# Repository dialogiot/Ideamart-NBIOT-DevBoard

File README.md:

### About the Board

The board is developed based on the [SIM7000C](http://www.simcomm2m.com/En/module/detail.aspx?id=167) and [SIM7000E](http://www.simcomm2m.com/En/module/detail.aspx?id=168) Modules as well as the Microcontroller ATMega 328 based on the most popular Arduino UNO PIN layout. Therefore this board is compatible with any shield that is compatible with the Arduino UNO

### Distribution
Any one can destribute or modify this deign. but originated souce should be published

### NB-IOT /GPS sample and SDK
[https://github.com/dialogiot/Dialog_NB-IOT_CAT-M](https://github.com/dialogiot/Dialog_NB-IOT_CAT-M)

#### Drivers

Download the [USB Drivers](https://github.com/botletics/SIM7000-LTE-Shield/wiki/SIM7000-USB-Drivers)
Note: Windows 10 users should use the Windows 8 Drivers

</img>

[View Image](https://idealab.ideamart.io/NBIOT-Dev-Board/img/features/board-diagram.jpg)

|No|PIN |Description|
|---|---|---|
| 1 | USB Port | Programing USB port for ATMEL Chip - PC driver may be required. Use Arduino USB cable or USB printer wire to connect with PC |
| 2 | FTDI | FTDI USB to Serial Converter FT232RL chip |
| 3 | LED2 | User programable LED |
| 4 | PIN Headers | Programable PIN headers to connect with micro controller. (Diagram 2 for more details) |
| 5 | Level Shifter | 1.8V to 5V voltage level shifter |
| 6 | SIM7000 | SIM7000 NB-IOT/eMTC/GSM/LTE Modem and GNSS Receiver |
| 7 | RF Antenna | RF mobile network antenna port for SIM7000 (u.fL) |
| 8 | GPS Antenna | GPS signal antenna port for SIM7000 (u.fL) |
| 9 | PPTC | PPTC resettable fuse for USB input over current protection (max 500mA) |
| 10 | DC Input | 2.1mm 7-12V DC power input |
| 11 | RESET | ATMEGA328P micro controller reset button |
| 12 | 3.3V Regulator | Lm1117 3.3V low dropout linear regulator (max 800ma)|
| 13 | 5V Regulator | LM1117 5V low dropout linear regulator (max 800mA) |
| 14 | PIN Headers | Programable PIN headers to connect with micro controller.(Diagram 2 for more details) |
| 15 | ATMEGA328P | ATMEGA328P micro controller |
| 16 | Power LED | Power indicator LED |
| 17 | ICSP Header | ICSP Header for Arduino programming |
| 18 | Modem Reset | SIM7000 modem hardware reset button |
| 19 | STAT LED | SIM7000 modem STAT LED indicator |
| 20 | Modem USB | SIM7000 modem USB port - firmware upgrade - Modem debug |
| 21 | PWR KEY | SIM7000 modem power key - Press 1.5sec to power up/down |
| 22 | Net Light | Power indicator LED |

## 2 What you Should know about the board

- ATMEGA328P µCU with FTDI USB to serial converter
- Same pinout as Arduino UNO
- Compatible with any Arduino UNO shield
- Programable with Arduino IDE
- NB-IoT/GSM/LTE/eMTC enabled SIM7000C/SIM7000E module onboard
- Separate USB interface for SIM7000 module
- GNSS (GPS,GLONASS and BeiDou/Compass, Galileo, QZSS)enabled 

> Separate USB interface can only be used for SIM7000 debug and firmware upgrades

- SIM7000C FDD-LTE B1/B3/B5/B8
- SIM7000E Tri-Band FDD-LTE B3/B8/B20/B28
- GSM/GPRS/EDGE 900/1800 MHz
- GNSS (GPS,GLONASS and BeiDou/Compass, Galileo, QZSS)
- LTE CAT-M1(eMTC) Uplink up to 375kbps, Downlink up to 300kbps
- NB-IoT Uplink up to 66kbps, Downlink up to 34kbps
- EDGE Class Uplink up to 236.8Kbps, Downlink up to 236.8Kbps
- GPRS Uplink up to 85.6Kbps, Downlink up to 85.6Kbps

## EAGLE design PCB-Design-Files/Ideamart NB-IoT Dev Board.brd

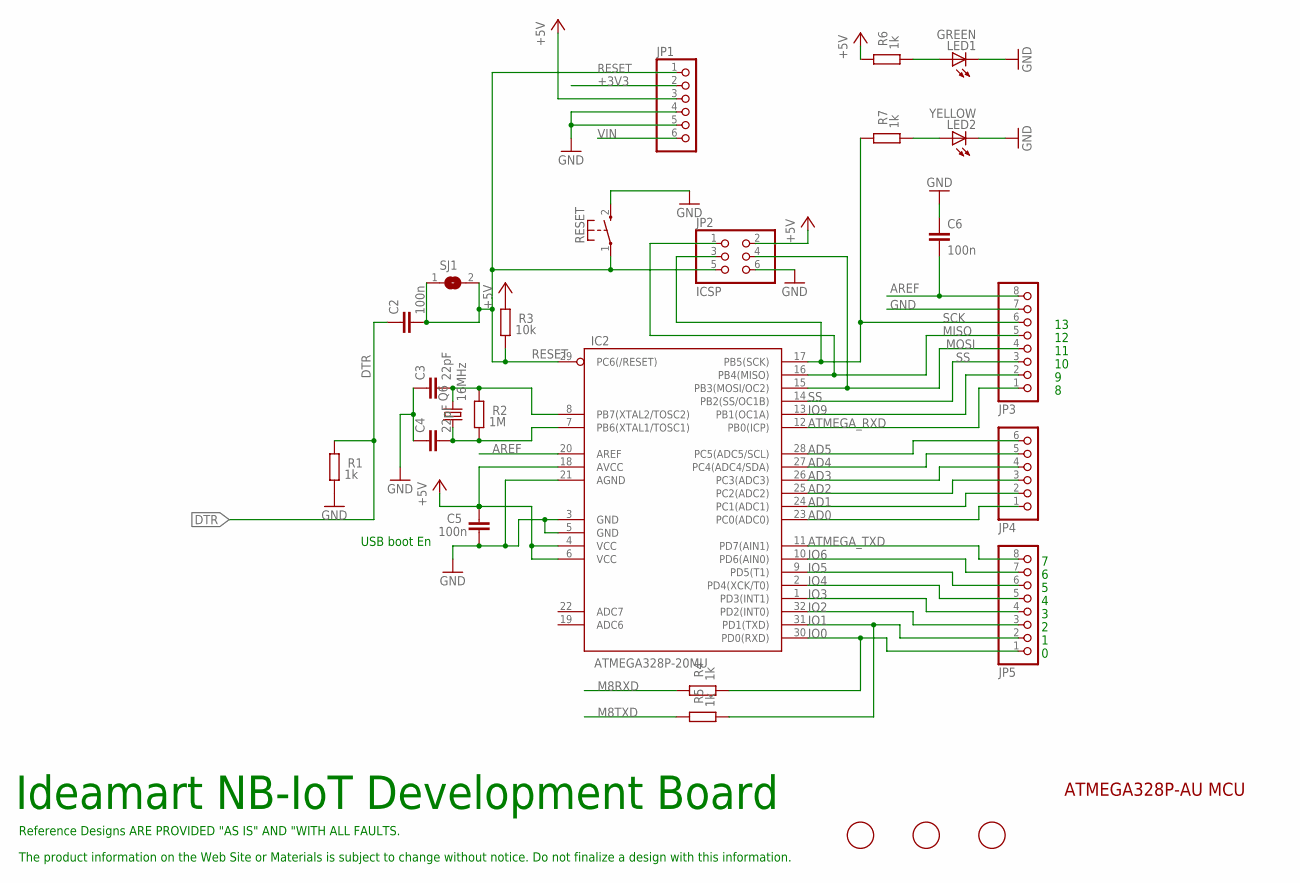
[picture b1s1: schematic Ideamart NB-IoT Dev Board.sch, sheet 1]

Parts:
C2, C5, C6: 100n; C0805
C3, C4: 22pF; C0805
IC2: ATMEGA328P-20MU; TQFP32-08
JP1, JP4: PINHD-1X6; 1X06
JP2: ICSP; 2X03
JP3, JP5: PINHD-1X8; 1X08
LED1: GREEN; CHIP-LED0805
LED2: YELLOW; CHIP-LED0805
M1, M2, M3: FIDUCIALMOUNT; FIDUCIA-MOUNT
Q6: 16MHz; CTS406
R1, R4, R5, R6, R7: 1k; R0805
R2: 1M; R0805
R3: 10k; R0805
RESET: KSS-2EG4430
SJ1: SJ

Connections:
+3V3: JP1.2; also elsewhere on the board
+5V: C5.2, IC2.4 (VCC), IC2.6 (VCC), IC2.18 (AVCC), JP1.3, JP2.2, R3.2, R6.2; also elsewhere on the board
AD0: IC2.23 (PC0(ADC0)), JP4.1
AD1: IC2.24 (PC1(ADC1)), JP4.2
AD2: IC2.25 (PC2(ADC2)), JP4.3
AD3: IC2.26 (PC3(ADC3)), JP4.4
AD4: IC2.27 (PC4(ADC4/SDA)), JP4.5
AD5: IC2.28 (PC5(ADC5/SCL)), JP4.6
AREF: C6.2, IC2.20 (AREF), JP3.8
ATMEGA_RXD: IC2.12 (PB0(ICP)), JP3.1; also elsewhere on the board
ATMEGA_TXD: IC2.11 (PD7(AIN1)), JP5.8; also elsewhere on the board
DTR: C2.1, R1.2; also elsewhere on the board
GND: C3.1, C4.1, C5.1, C6.1, IC2.3 (GND), IC2.5 (GND), IC2.21 (AGND), JP1.4, JP1.5, JP2.6, JP3.7, LED1.C, LED2.C, R1.1, RESET.2 (S); also elsewhere on the board
IO0: IC2.30 (PD0(RXD)), JP5.1, R4.1
IO1: IC2.31 (PD1(TXD)), JP5.2, R5.1
IO2: IC2.32 (PD2(INT0)), JP5.3
IO3: IC2.1 (PD3(INT1)), JP5.4
IO4: IC2.2 (PD4(XCK/T0)), JP5.5
IO5: IC2.9 (PD5(T1)), JP5.6
IO6: IC2.10 (PD6(AIN0)), JP5.7
IO9: IC2.13 (PB1(OC1A)), JP3.2
M8RXD: R4.2; also elsewhere on the board
M8TXD: R5.2; also elsewhere on the board
MISO: IC2.16 (PB4(MISO)), JP2.1, JP3.5
MOSI: IC2.15 (PB3(MOSI/OC2)), JP2.4, JP3.4; also elsewhere on the board
unnamed: LED2.A, R7.1
unnamed: LED1.A, R6.1
RESET: C2.2, IC2.29 (PC6(/RESET)), JP1.1, JP2.5, R3.1, RESET.1, SJ1.1, SJ1.2
SCK: IC2.17 (PB5(SCK)), JP2.3, JP3.6, R7.2; also elsewhere on the board
SS: IC2.14 (PB2(SS/OC1B)), JP3.3
VIN: JP1.6; also elsewhere on the board
XTAL1: C4.2, IC2.7 (PB6(XTAL1/TOSC1)), Q6.1, R2.1
XTAL2: C3.2, IC2.8 (PB7(XTAL2/TOSC2)), Q6.3 (2), R2.2

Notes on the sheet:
Ideamart NB-IoT Development Board
USB boot En
Reference Designs ARE PROVIDED "AS IS" AND "WITH ALL FAULTS.
The product information on the Web Site or Materials is subject to change without notice. Do not finalize a design with this information.
ATMEGA328P-AU MCU

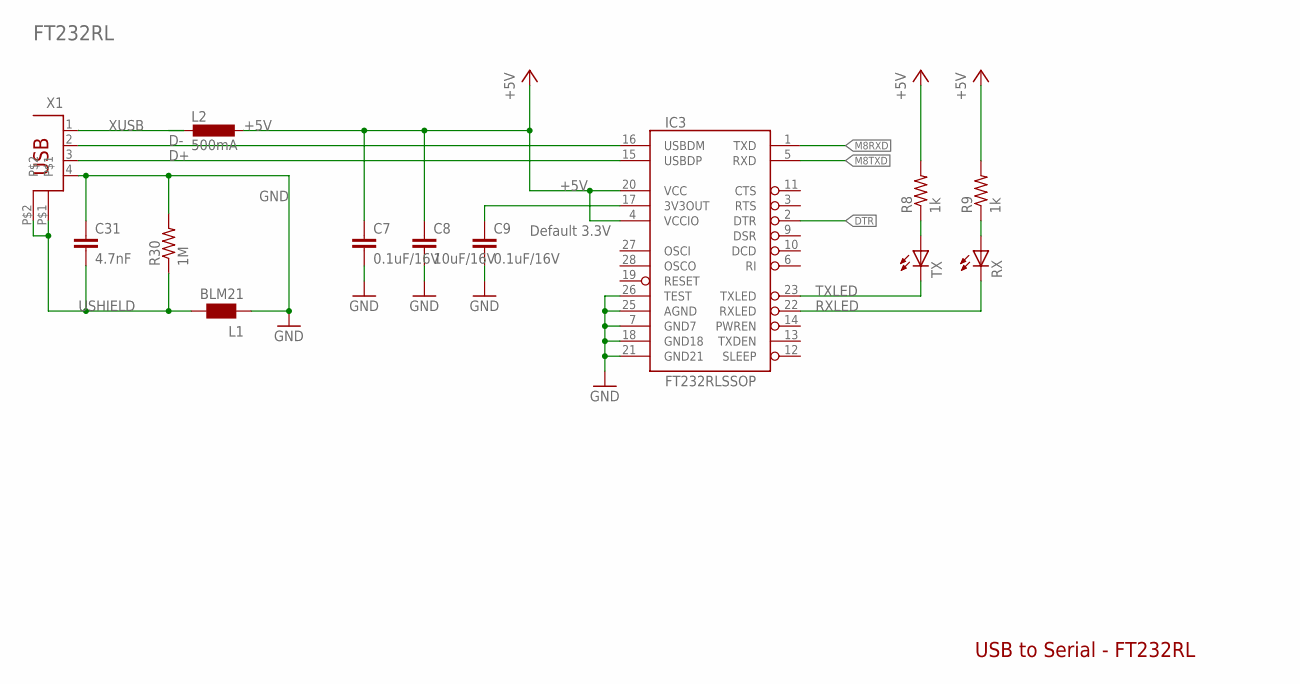
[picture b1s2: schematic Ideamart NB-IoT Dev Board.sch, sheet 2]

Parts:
C7, C9: 0.1uF/16V; C0805K
C8: 10uF/16V; C0805K
C31: 4.7nF; C0805K
IC3: FT232RLSSOP; SSOP28DB
L1: BLM21; 0805
L2: 500mA; L1812
R8, R9: 1k; M0805
R30: 1M; M0805
RX: LEDCHIP-LED0805; CHIP-LED0805
TX: LEDCHIP-LED0805; CHIP-LED0805
X1: PN61729

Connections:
+5V: C7.1, C8.1, IC3.4 (VCCIO), IC3.20 (VCC), L2.1, R8.2, R9.2; also elsewhere on the board
D+: IC3.15 (USBDP), X1.3
D-: IC3.16 (USBDM), X1.2
DTR: IC3.2 (DTR); also elsewhere on the board
GND: C7.2, C8.2, C9.2, C31.1, IC3.7 (GND7), IC3.18 (GND18), IC3.21 (GND21), IC3.25 (AGND), IC3.26 (TEST), L1.1, R30.2, X1.4; also elsewhere on the board
M8RXD: IC3.1 (TXD); also elsewhere on the board
M8TXD: IC3.5 (RXD); also elsewhere on the board
unnamed: C9.1, IC3.17 (3V3OUT)
unnamed: R8.1, TX.A
unnamed: R9.1, RX.A
RXLED: IC3.22 (RXLED), RX.C
TXLED: IC3.23 (TXLED), TX.C
USHIELD: C31.2, L1.2, R30.1, X1.P$1, X1.P$2
XUSB: L2.2, X1.1

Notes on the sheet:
Default 3.3V
USB to Serial - FT232RL
FT232RL

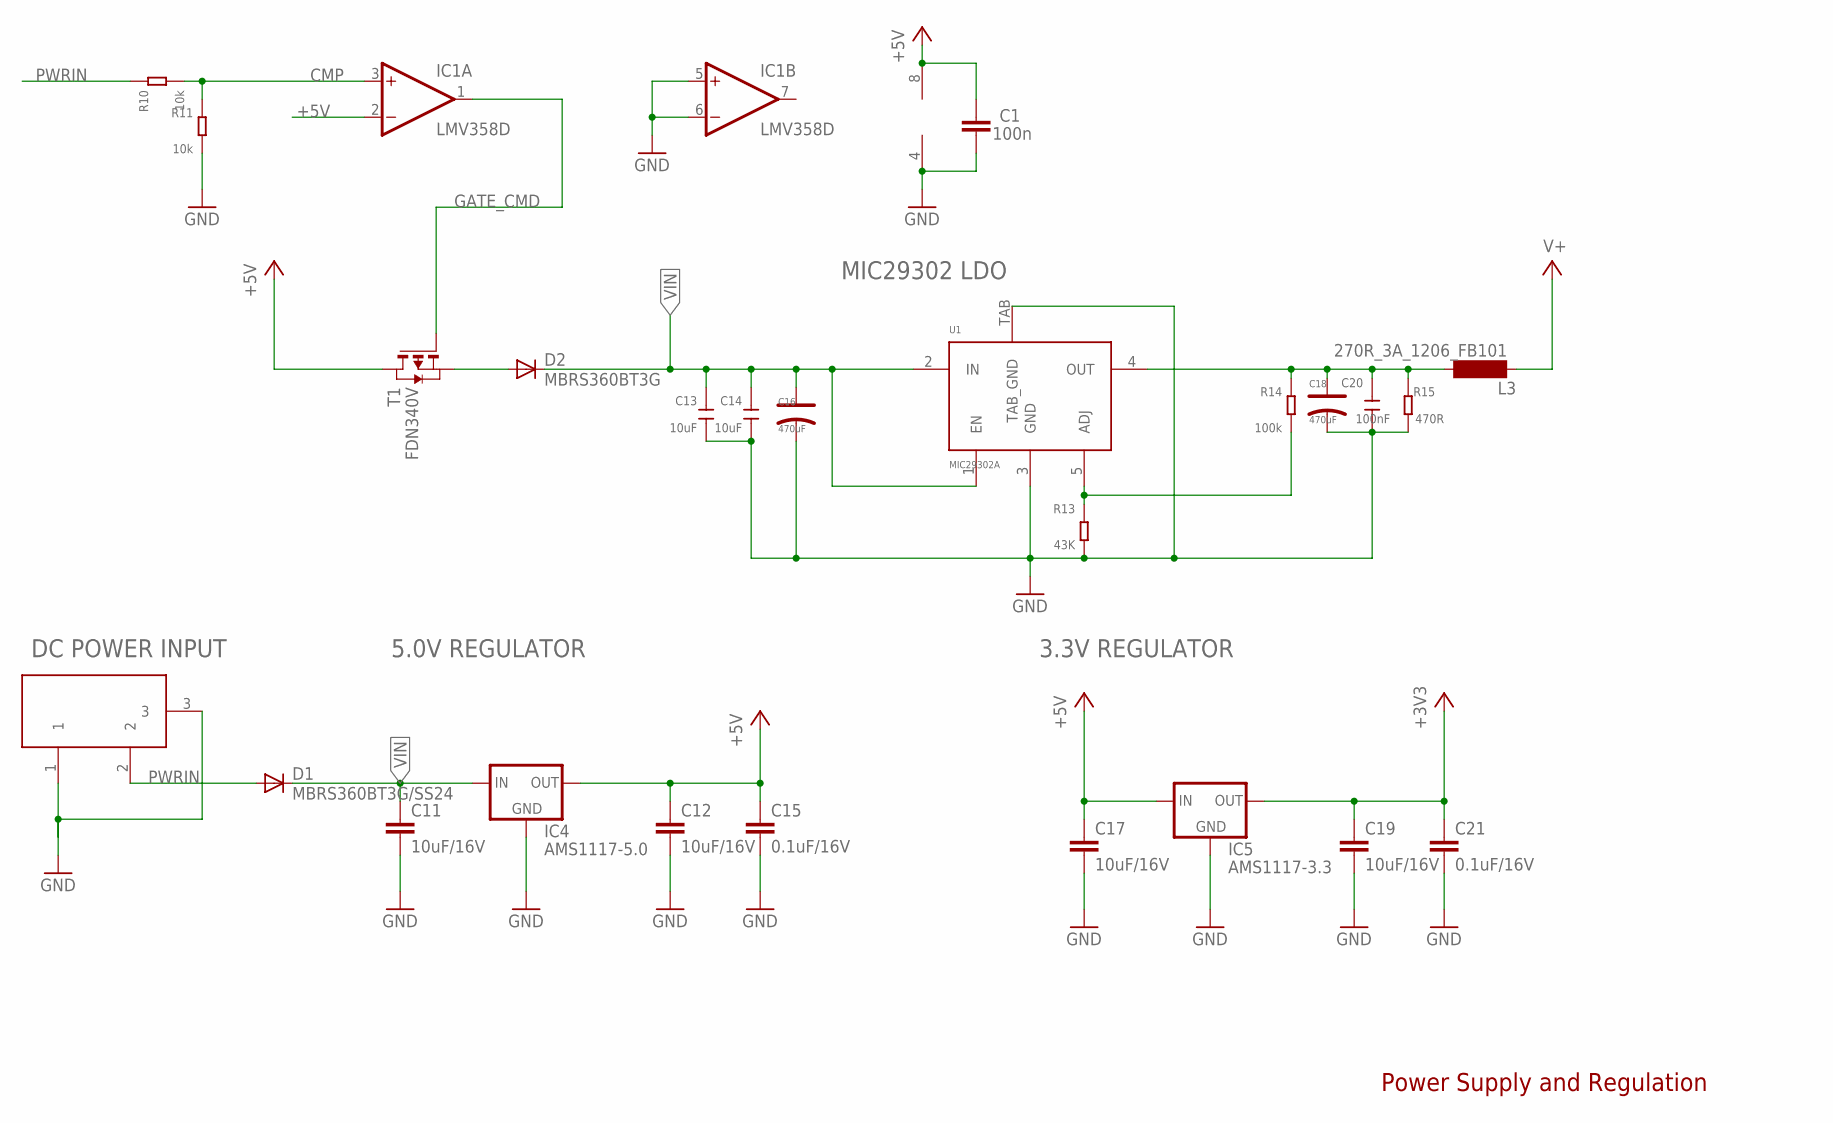
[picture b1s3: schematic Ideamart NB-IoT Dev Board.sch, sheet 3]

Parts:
C1: 100n; C0805
C10: DC21MMX; DC-21MM
C11, C12, C17, C19: 10uF/16V; C0805K
C13, C14: 10uF; 0805
C15, C21: 0.1uF/16V; C0805K
C16, C18: 470uF; AVX_D
C20: 100nF; 0805
D1: MBRS360BT3G/SS24; SMB
D2: MBRS360BT3G; SMB
IC1: LMV358D; SO08
IC4: AMS1117-5.0; SOT223
IC5: AMS1117-3.3; SOT223
L3: 270R_3A_1206_FB101; SM-1206
R10, R11: 10k; 0805
R13: 43K; 0805
R14: 100k; 0805
R15: 470R; 0805
T1: FDN340V; SOT-23
U1: MIC29302A; TO-263A

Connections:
+3V3: C19.1, C21.1, IC5.2 (OUT); also elsewhere on the board
+5V: C1.2, C12.1, C15.1, C17.1, IC1.2 (-IN), IC1.8 (V+), IC4.2 (OUT), IC5.3 (IN), T1.1 (D); also elsewhere on the board
CMP: IC1.3 (+IN), R10.1, R11.2
GATE_CMD: IC1.1 (OUT), T1.3 (G)
GND: C1.1, C10.1, C10.3, C11.2, C12.2, C13.1, C14.1, C15.2, C16.-, C17.2, C18.-, C19.2, C20.1, C21.2, IC1.4 (V-), IC1.5 (+IN), IC1.6 (-IN), IC4.1 (GND), IC5.1 (GND), R11.1, R13.1, R15.1, U1.3 (GND), U1.TAB (TAB_GND); also elsewhere on the board
unnamed: R13.2, R14.1, U1.5 (ADJ)
unnamed: D2.A, T1.2 (S)
PWRIN: C10.2, D1.A, R10.2
V+: L3.1; also elsewhere on the board
VIN: C11.1, C13.2, C14.2, C16.+, D1.C, D2.C, IC4.3 (IN), U1.1 (EN), U1.2 (IN); also elsewhere on the board
VOUT: C18.+, C20.2, L3.2, R14.2, R15.2, U1.4 (OUT)

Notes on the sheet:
DC POWER INPUT
Power Supply and Regulation
3.3V REGULATOR
MIC29302 LDO
5.0V REGULATOR

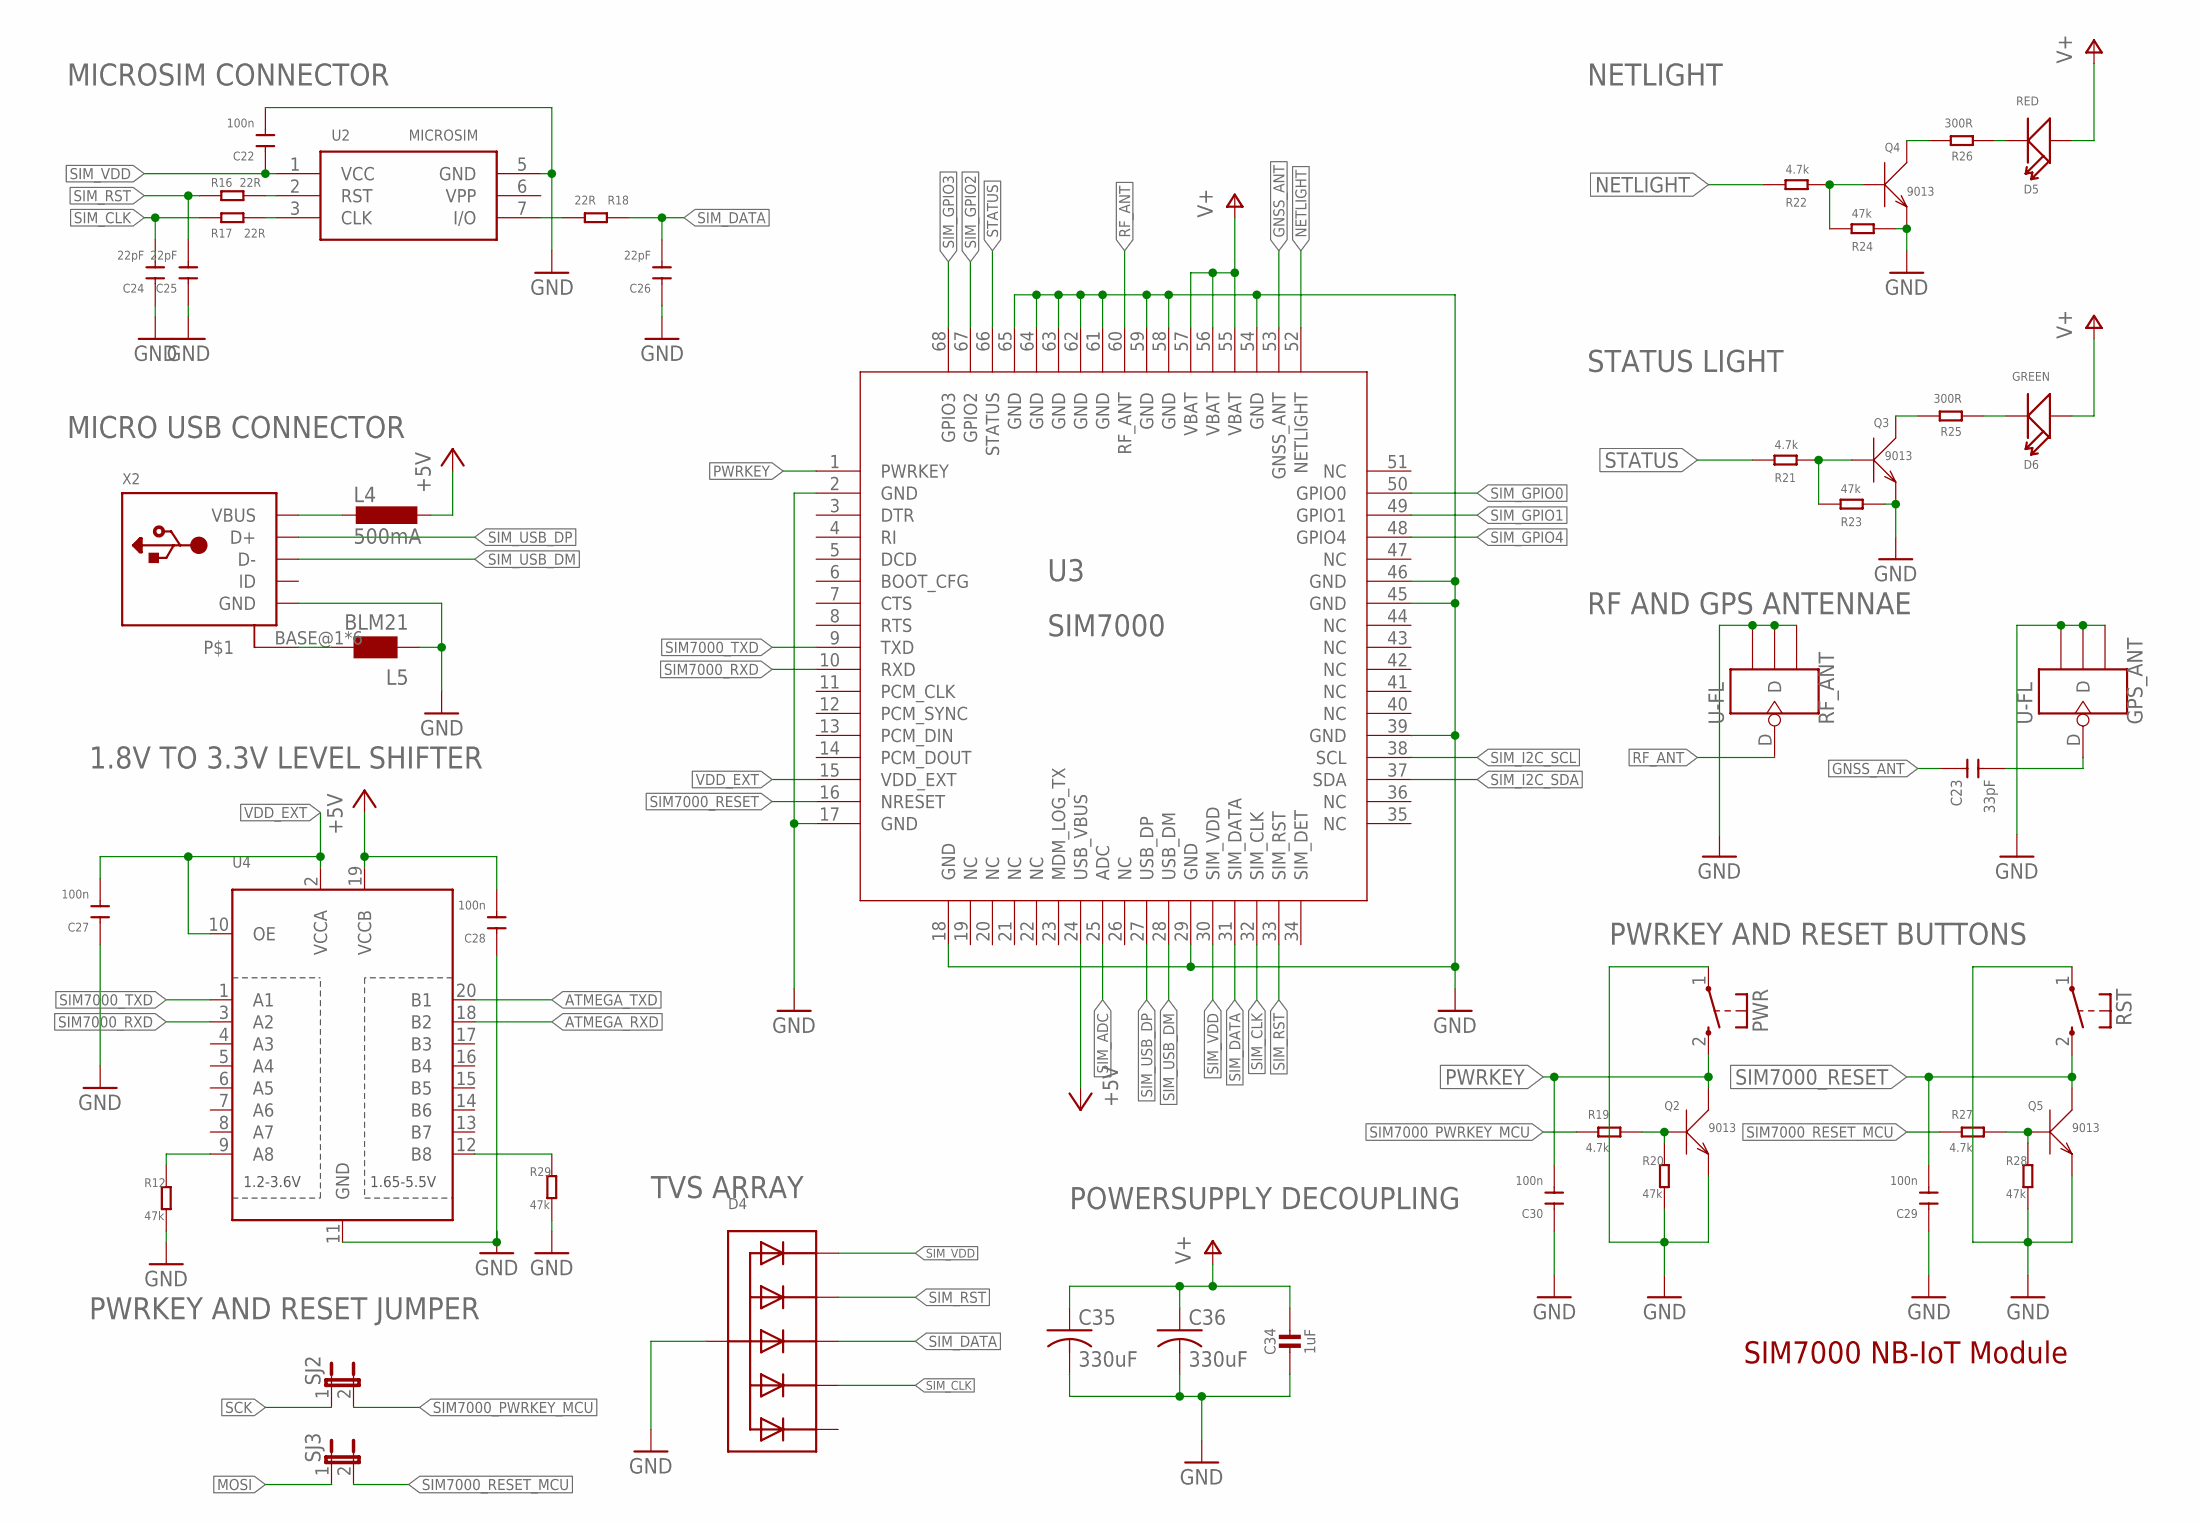
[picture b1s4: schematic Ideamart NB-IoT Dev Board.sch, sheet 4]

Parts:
C22, C27, C28, C29, C30: 100n; 0805
C23: 33pF; 0805
C24, C25, C26: 22pF; 0805
C34: 1uF; _0805
C35, C36: 330uF; C1210
D4: TVSARRAY_5LANE; SOT363
D5: RED; LED-0805
D6: GREEN; LED-0805
GPS_ANT: U-FL; 4P-U-FL
L4: 500mA; L1812
L5: BLM21; 0805
PWR: KSS-2EG4430
Q2, Q3, Q4, Q5: 9013; SOT23
R12, R20, R23, R24, R28, R29: 47k; 0805
R16, R17, R18: 22R; 0805
R19, R21, R22, R27: 4.7k; 0805
R25, R26: 300R; 0805
RF_ANT: U-FL; 4P-U-FL
RST: KSS-2EG4430
SJ2, SJ3: SPARKFUN-PASSIVES_JUMPER-PTH-2-NC; SPARKFUN-PASSIVES_PTH-JUMPER-NC_BOTTOM_NO_SILK
U2: MICROSIM
U3: SIM7000
U4: TXB0108PWR; TSSOP20
X2: USB_MICRO_20329_V2; 4UCONN_20329_V2

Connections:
+5V: C28.2, L4.1, U3.24 (USB_VBUS), U4.19 (VCCB); also elsewhere on the board
ATMEGA_RXD: U4.18 (B2); also elsewhere on the board
ATMEGA_TXD: U4.20 (B1); also elsewhere on the board
GND: C22.2, C24.1, C25.1, C26.1, C27.1, C28.1, C29.1, C30.1, C34.2, C35.2, C36.2, D4.2 (A), GPS_ANT.GND1, GPS_ANT.GND2, GPS_ANT.GND3, L5.1, PWR.1, Q2.2 (E), Q3.2 (E), Q4.2 (E), Q5.2 (E), R12.2, R20.2, R23.2, R24.2, R28.2, R29.2, RF_ANT.GND1, RF_ANT.GND2, RF_ANT.GND3, RST.1, U2.5 (GND), U3.2 (GND), U3.17 (GND), U3.18 (GND), U3.29 (GND), U3.39 (GND), U3.45 (GND), U3.46 (GND), U3.54 (GND), U3.58 (GND), U3.59 (GND), U3.61 (GND), U3.62 (GND), U3.63 (GND), U3.64 (GND), U3.65 (GND), U4.11 (GND), X2.GND; also elsewhere on the board
GNSS_ANT: C23.2, U3.53 (GNSS_ANT)
MOSI: SJ3.1; also elsewhere on the board
unnamed: Q3.3 (C), R25.2
unnamed: D6.-, R25.1
unnamed: Q3.1 (B), R21.2, R23.1
unnamed: R18.2, U2.7 (I/O)
unnamed: R17.1, U2.3 (CLK)
unnamed: R16.1, U2.2 (RST)
unnamed: Q5.1 (B), R27.2, R28.1
unnamed: L4.2, X2.VBUS
unnamed: Q4.3 (C), R26.2
unnamed: D5.-, R26.1
unnamed: Q4.1 (B), R22.2, R24.1
unnamed: C23.1, GPS_ANT.D
unnamed: R12.1, U4.9 (A8)
unnamed: R29.1, U4.12 (B8)
unnamed: L5.2, X2.BASE@1, X2.BASE@2, X2.SPRT@1, X2.SPRT@2, X2.SPRT@3, X2.SPRT@4
unnamed: Q2.1 (B), R19.2, R20.1
NETLIGHT: R22.1, U3.52 (NETLIGHT)
PWRKEY: C30.2, PWR.2 (S), Q2.3 (C), U3.1 (PWRKEY)
RF_ANT: RF_ANT.D, U3.60 (RF_ANT)
SCK: SJ2.1; also elsewhere on the board
SIM7000_PWRKEY_MCU: R19.1, SJ2.2
SIM7000_RESET: C29.2, Q5.3 (C), RST.2 (S), U3.16 (NRESET)
SIM7000_RESET_MCU: R27.1, SJ3.2
SIM7000_RXD: U3.10 (RXD), U4.3 (A2)
SIM7000_TXD: U3.9 (TXD), U4.1 (A1)
SIM_ADC: U3.25 (ADC)
SIM_CLK: C24.2, D4.5 (C4), R17.2, U3.32 (SIM_CLK)
SIM_DATA: C26.2, D4.4 (C3), R18.1, U3.31 (SIM_DATA)
SIM_GPIO0: U3.50 (GPIO0)
SIM_GPIO1: U3.49 (GPIO1)
SIM_GPIO2: U3.67 (GPIO2)
SIM_GPIO3: U3.68 (GPIO3)
SIM_GPIO4: U3.48 (GPIO4)
SIM_I2C_SCL: U3.38 (SCL)
SIM_I2C_SDA: U3.37 (SDA)
SIM_RST: C25.2, D4.3 (C2), R16.2, U3.33 (SIM_RST)
SIM_USB_DM: U3.28 (USB_DM), X2.D-
SIM_USB_DP: U3.27 (USB_DP), X2.D+
SIM_VDD: C22.1, D4.1 (C1), U2.1 (VCC), U3.30 (SIM_VDD)
STATUS: R21.1, U3.66 (STATUS)
V+: C34.1, C35.1, C36.1, D5.+, D6.+, U3.55 (VBAT), U3.56 (VBAT), U3.57 (VBAT); also elsewhere on the board
VDD_EXT: C27.2, U3.15 (VDD_EXT), U4.2 (VCCA), U4.10 (OE)

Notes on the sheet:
TVS ARRAY
MICROSIM CONNECTOR
SIM7000 NB-IoT Module
MICRO USB CONNECTOR
NETLIGHT
STATUS LIGHT
RF AND GPS ANTENNAE
PWRKEY AND RESET BUTTONS
PWRKEY AND RESET JUMPER
1.8V TO 3.3V LEVEL SHIFTER
POWERSUPPLY DECOUPLING

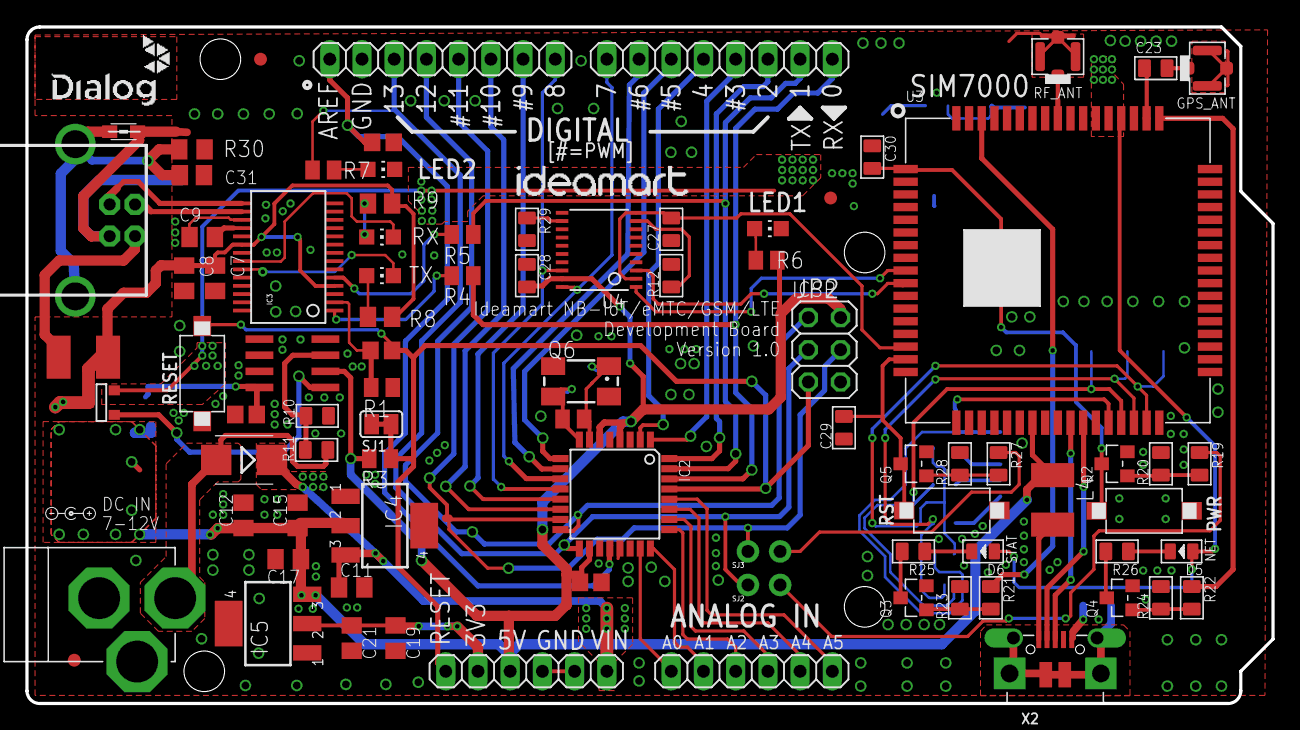
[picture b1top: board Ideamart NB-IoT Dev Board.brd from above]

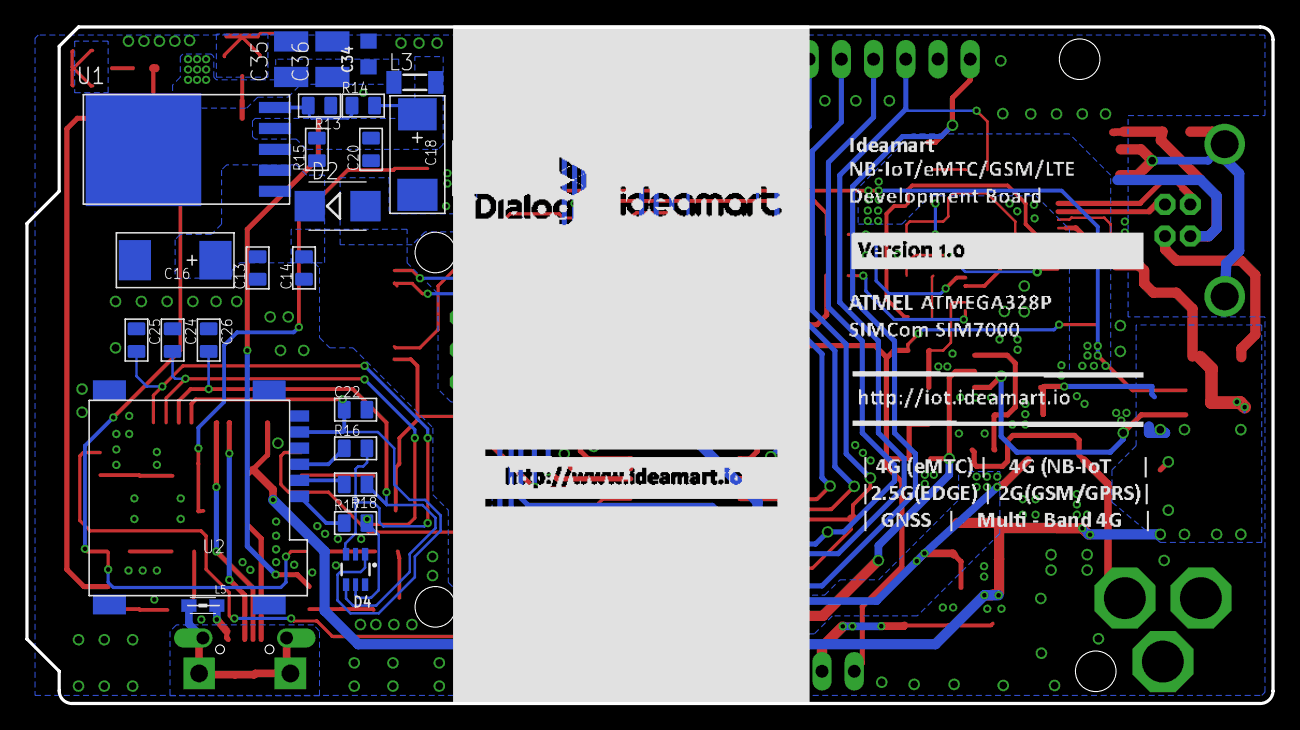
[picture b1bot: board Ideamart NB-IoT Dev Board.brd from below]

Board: 2 copper layers, 98.2 x 53.3 mm, 111 parts (26 on the bottom side), 82 nets.

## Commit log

2018-03-30 Adding design files
2018-03-31 added photos
2021-05-25 fix readme image url
